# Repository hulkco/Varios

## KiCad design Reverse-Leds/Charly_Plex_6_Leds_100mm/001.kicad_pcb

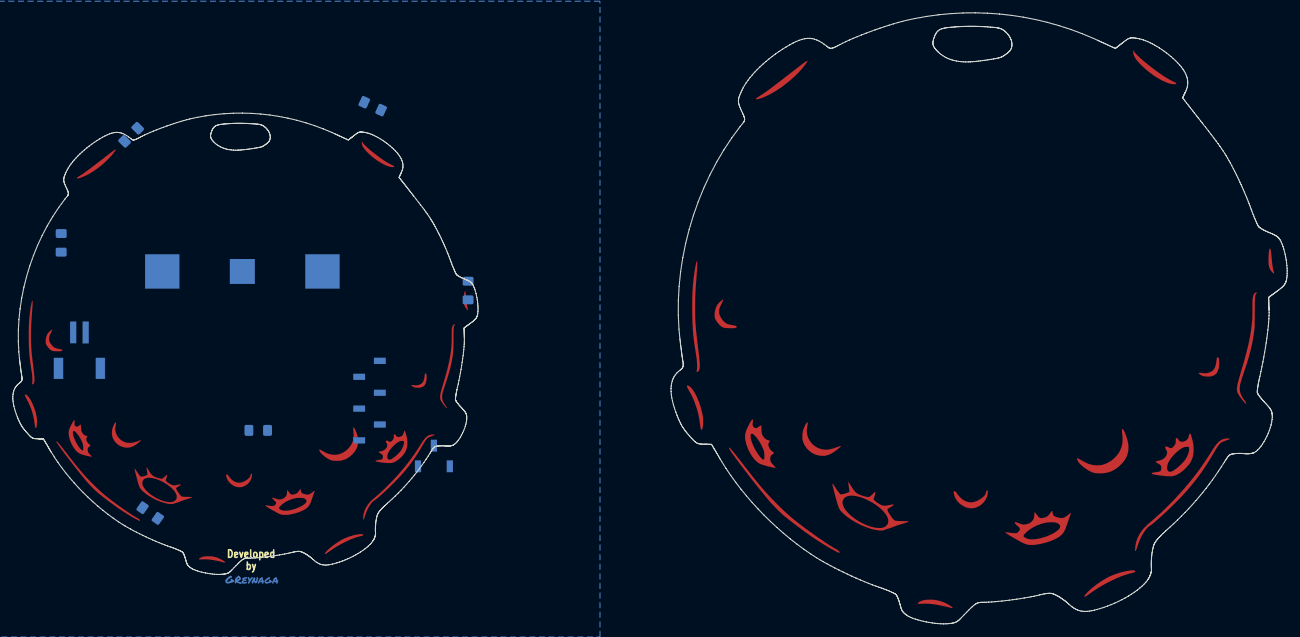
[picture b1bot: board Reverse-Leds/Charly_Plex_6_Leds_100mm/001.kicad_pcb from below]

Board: 2 copper layers, 74.3 x 73.7 mm, 12 parts (10 on the bottom side), 5 nets, no tracks yet.

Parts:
BT1: Battery_Cell; S8211R
D1, D2, D3, D4, D5, D6: LED; LED_1206_Reverse
J1: Conn_01x02; JST-S2B-PH-SM4-TB
J2: Conn_01x06_x03; Digispark_SMD_Reverse
Ref**: Val**; Moon_6_Leds_75mm
U1: PCB; Moon_6_Leds_100mm
U2: Firma; firma_Cu_Mask

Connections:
/PB_0: D1.1, D2.2, D5.1, D6.2, J2.1
/PB_1: D1.2, D2.1, D3.1, D4.2, J2.2
/PB_4: D3.2, D4.1, D5.2, D6.1, J2.5
GND: BT1.2, J1.2, J2.8
VIN: BT1.1, J1.1, J2.7

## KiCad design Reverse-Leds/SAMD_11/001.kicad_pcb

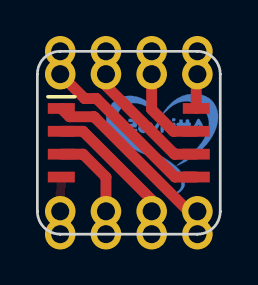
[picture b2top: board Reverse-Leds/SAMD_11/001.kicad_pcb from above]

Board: 2 copper layers, 10.2 x 10.2 mm, 5 parts (0 on the bottom side), 8 nets.

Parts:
IC1: ATTINY85-20SU; SOT127P798X216-8N
J1: Conn_01x04; Attiny85_Socket_Castell_Up
J2: Conn_01x04; Attiny85_Socket_Castell_Down
Ref**: Val**; Heart_Firma
Ref**#2: Val**; Heart

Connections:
GND: IC1.4, J2.1
unnamed: IC1.1, J2.4
unnamed: IC1.2, J2.3
unnamed: IC1.3, J2.2
unnamed: IC1.5, J1.1
unnamed: IC1.6, J1.2
unnamed: IC1.7, J1.3
VCC: IC1.8, J1.4

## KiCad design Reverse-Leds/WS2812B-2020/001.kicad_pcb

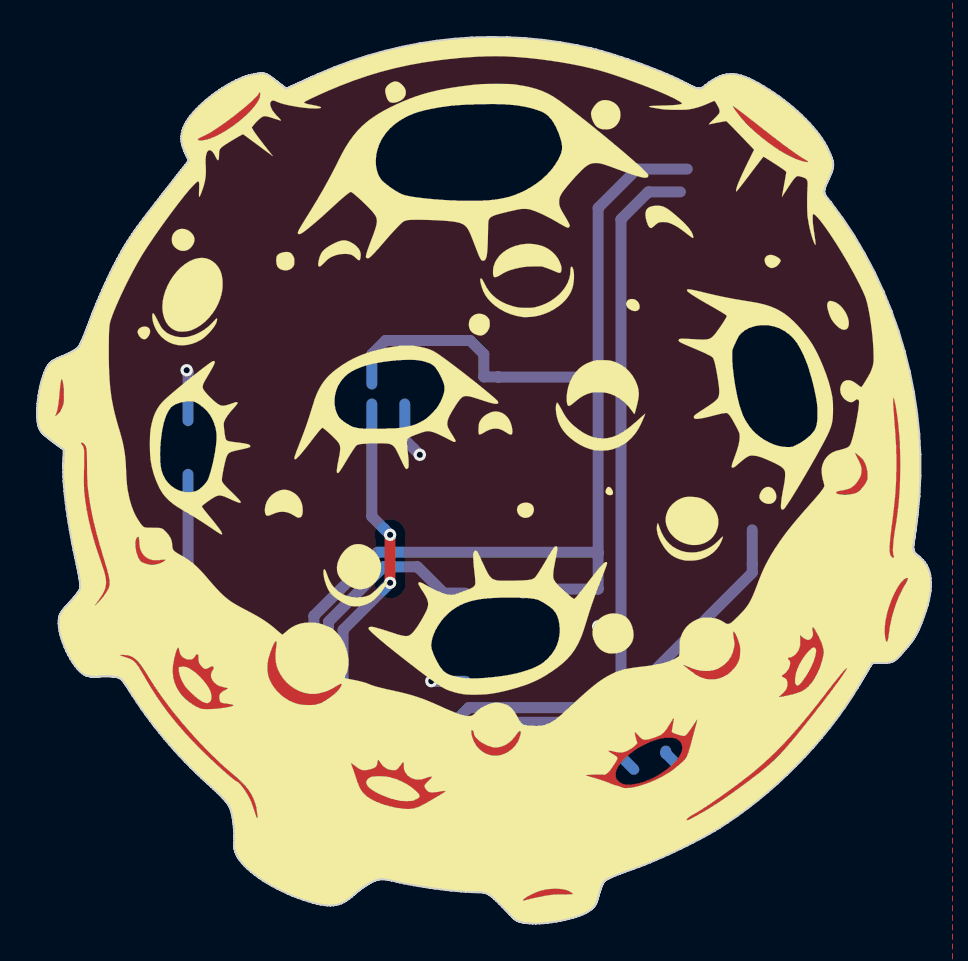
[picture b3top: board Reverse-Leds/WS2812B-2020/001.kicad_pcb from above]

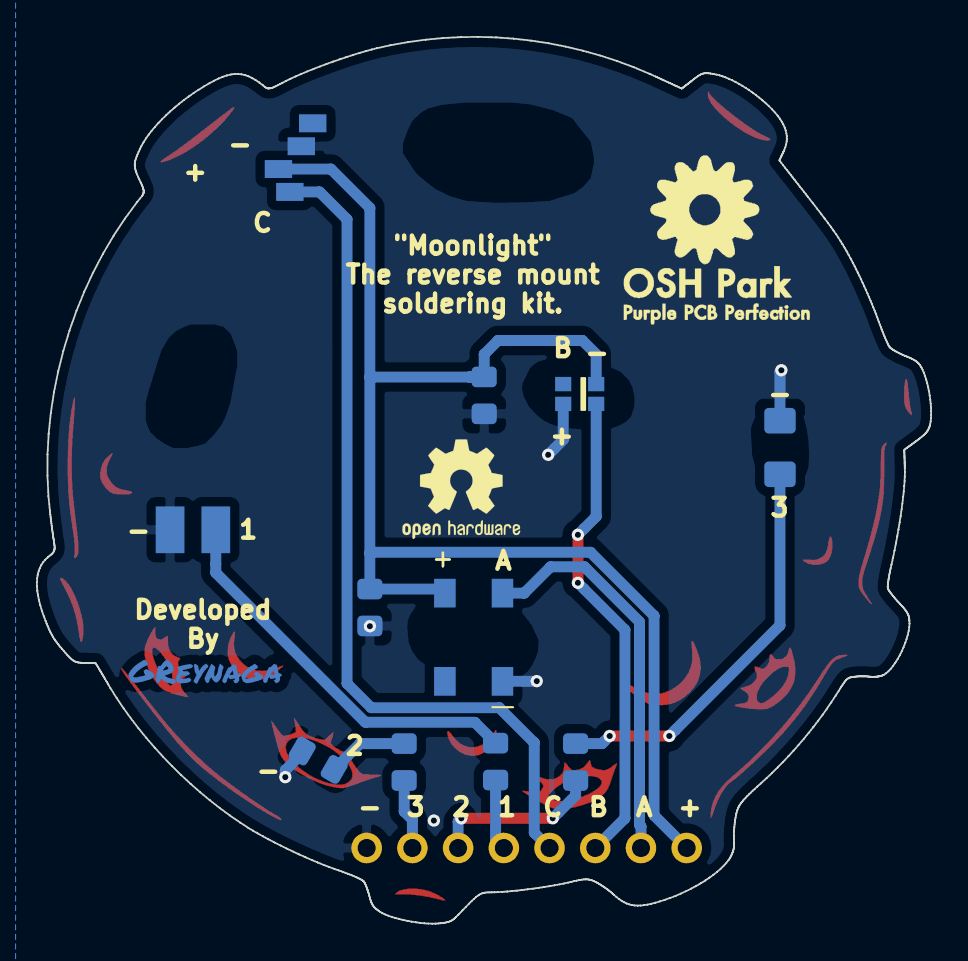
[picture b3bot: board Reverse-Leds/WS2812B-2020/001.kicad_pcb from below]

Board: 2 copper layers, 49.7 x 49.3 mm, 15 parts (14 on the bottom side), 11 nets.

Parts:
C1, C2: 100nF; C_0805_2012Metric_Pad1.15x1.40mm_HandSolder
D1: LED; LED_D5.0mm_Reverse
D2: LED; LED_1206_Reverse
D3: LED; LED_0805_Reverse
J2: Conn_01x08; 1x08_P2.54mm_Vertical
LED1: WS2812B-Reverse; WS2812B__Reverse
LED2: WS2812B-2020-Reverse; WS2812B-2020_Reverse
LED3: PL9223-F8-Reverse; P9823_Reverse_Mount
PP-G***: PP-LOGO; OSHpark-1-1200
R1, R2, R3: 330; R_0805_2012Metric_Pad1.15x1.40mm_HandSolder
U1: PCB; Regla_Leds
svg2mod: G***; firma_Cu_Mask

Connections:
/Led_1: J2.5, R1.2
/Led_2: J2.6, R2.2
/Led_3: J2.7, R3.2
/Port_A: J2.2, LED1.2
/Port_B: J2.3, LED2.2
/Port_C: J2.4, LED3.2
GND: C1.2, C2.2, D1.1, D2.1, D3.1, J2.8, LED1.3, LED2.3, LED3.3
unnamed: D1.2, R1.1
unnamed: D2.2, R2.1
unnamed: D3.2, R3.1
VCC: C1.1, C2.1, J2.1, LED1.1, LED2.1, LED3.1

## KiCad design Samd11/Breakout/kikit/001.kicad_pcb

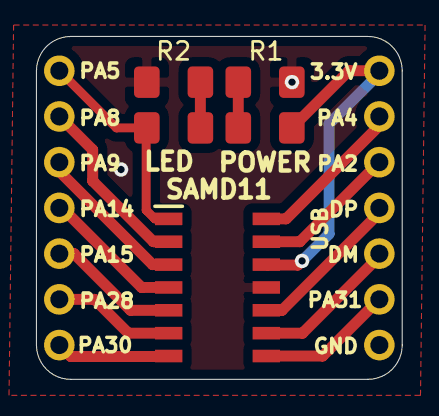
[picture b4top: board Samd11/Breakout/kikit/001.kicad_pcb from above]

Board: 2 copper layers, 20.3 x 19.0 mm, 7 parts (0 on the bottom side), 16 nets.

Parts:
D1: POWER; LED_1206_3216Metric_Pad1.42x1.75mm_HandSolder
D2: LED; LED_1206_3216Metric_Pad1.42x1.75mm_HandSolder
IC2: ATSAMD11C14A-SSUT; SOIC127P600X175-14N
J1, J2: Conn_01x07; PinHeader_1x07_P2.54mm_Vertical
R1, R2: 1K; R_1206_3216Metric_Pad1.42x1.75mm_HandSolder

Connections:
+3V3: D1.2, IC2.12, J2.1
/PA02: IC2.13, J2.3
/PA04: IC2.14, J2.2
/PA05: D2.2, IC2.1, J1.1
/PA08: IC2.2, J1.2
/PA09: IC2.3, J1.3
/PA14: IC2.4, J1.4
/PA15: IC2.5, J1.5
/PA24: IC2.9, J2.5
/PA25: IC2.10, J2.4
/PA28: IC2.6, J1.6
/PA30: IC2.7, J1.7
/PA31: IC2.8, J2.6
GND: IC2.11, J2.7, R1.2, R2.2
unnamed: D1.1, R1.1
unnamed: D2.1, R2.1
